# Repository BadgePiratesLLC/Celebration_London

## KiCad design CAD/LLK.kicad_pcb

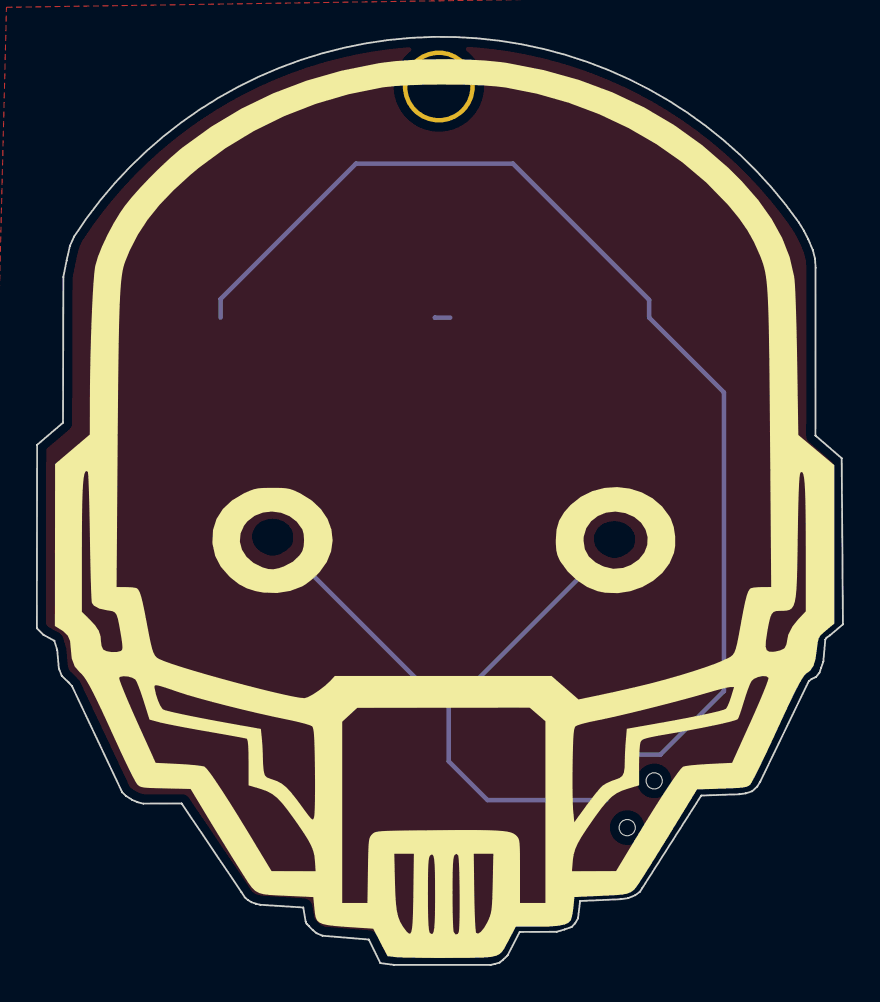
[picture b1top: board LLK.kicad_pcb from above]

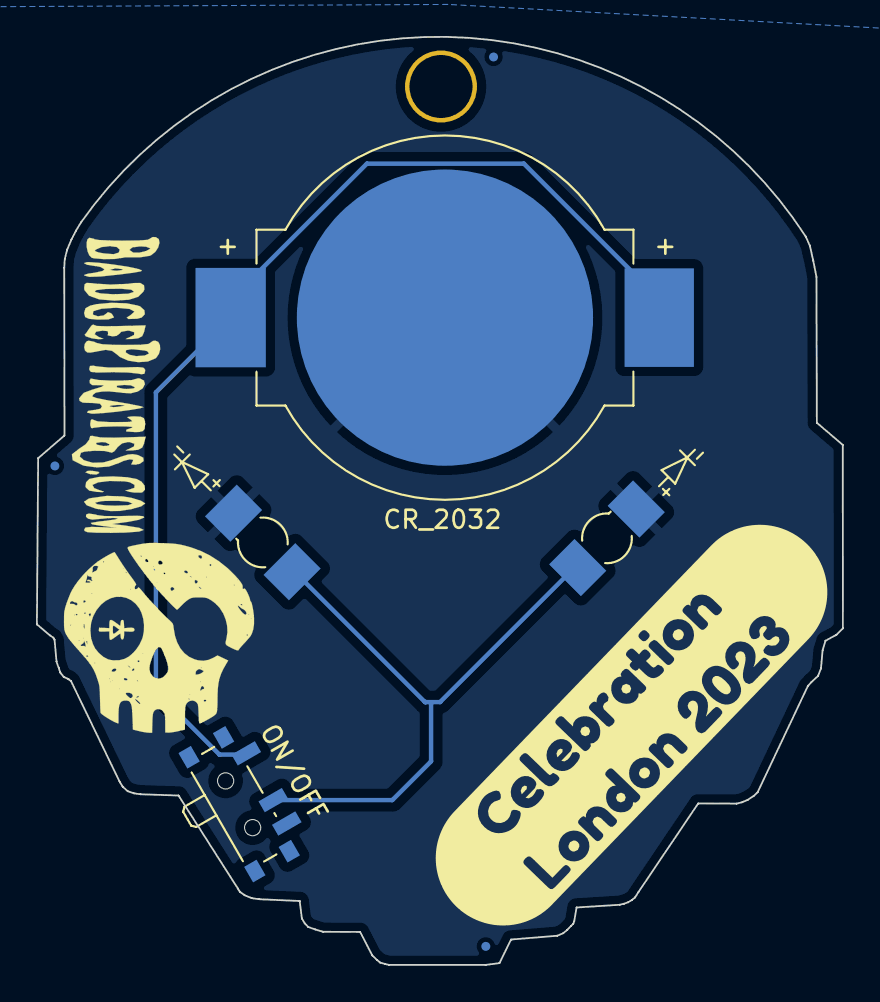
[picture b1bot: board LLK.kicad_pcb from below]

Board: 2 copper layers, 44.8 x 51.6 mm, 5 parts (3 on the bottom side), 3 nets.

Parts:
BT1: Battery_Cell; BatteryHolder_MPD_BC2003_1x2032_Fixed
D1, D2: LED; LED_Osram_Lx_P47F_D2mm_ReverseMount_Proper_Mask Only
ON/OFF: SW_SPST; SW_SPDT_PCM12
kibuzzard-639739B8: G***; kibuzzard-639739B8

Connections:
GND: BT1.2 (-), D1.1 (K), D2.1 (K)
unnamed: BT1.1 (+), ON/OFF.1 (A)
unnamed: D1.2 (A), D2.2 (A), ON/OFF.2 (B)

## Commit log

2023-01-04 gerbers
